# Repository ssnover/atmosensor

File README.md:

# atmosensor
This is a simple project for measuring and recording air quality data from an embedded device.

## Components
* [`atmosensor-fw`](atmosensor-fw/README.md) This contains the embedded firmware application which reads from
the sensors and communicates the data over USB.
* `atmosensor-host-apps` Linux-based applications for interacting with the firmware app.
  * `atmosensor-tui` Text user interface for sending and receiving commands via USB.
* `atmosensor-kicad` KiCAD schematic and PCB layout for the hardware which connects
to the sensors.
* `usb-protocol` Documentation of the protocol being used for communicating between
the host application and the embedded firmware.

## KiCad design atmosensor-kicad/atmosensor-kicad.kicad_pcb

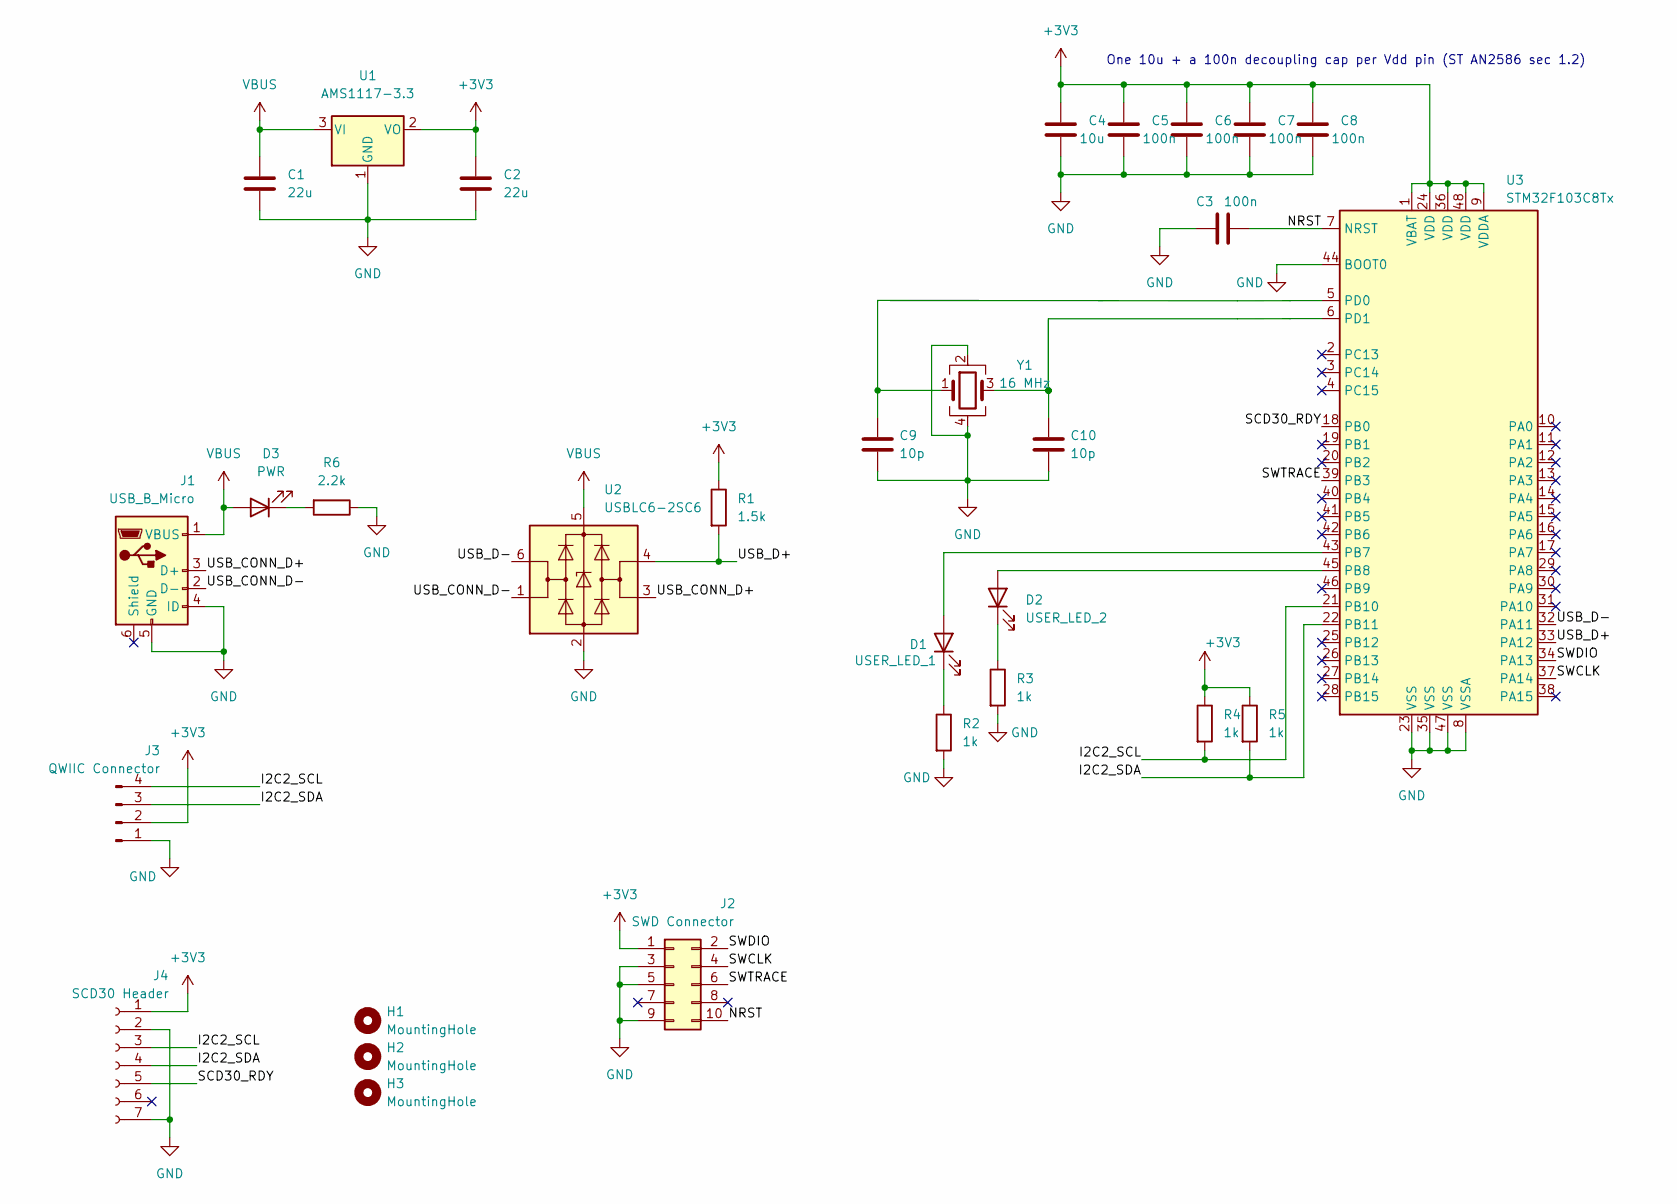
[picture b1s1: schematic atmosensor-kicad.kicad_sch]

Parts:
C1, C2: 22u; C_0603_1608Metric
C3, C5, C6, C7, C8: 100n; C_0402_1005Metric
C4: 10u; C_0603_1608Metric
C9, C10: 10p; C_0402_1005Metric
D1: USER_LED_1; LED_0402_1005Metric
D2: USER_LED_2; LED_0402_1005Metric
D3: PWR; LED_0402_1005Metric
H1, H2, H3: MountingHole; MountingHole_2.2mm_M2
J1: USB_B_Micro; USB_Micro-B_Amphenol_10103594-0001LF_Horizontal
J2: SWD Connector; PinHeader_2x05_P1.27mm_Vertical_SMD
J3: QWIIC Connector; JST_SM04B-SRSS-TB(LF)(SN)
J4: SCD30 Header; PinSocket_1x07_P2.54mm_Vertical
R1: 1.5k; R_0402_1005Metric
R2, R3, R4, R5: 1k; R_0402_1005Metric
R6: 2.2k; R_0402_1005Metric
U1: AMS1117-3.3; SOT-223-3_TabPin2
U2: USBLC6-2SC6; SOT-23-6
U3: STM32F103C8Tx; LQFP-48_7x7mm_P0.5mm
Y1: 16 MHz; Crystal_SMD_3225-4Pin_3.2x2.5mm

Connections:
+3V3: C2.1, C4.1, C5.1, C6.1, C7.1, C8.1, J2.1, J3.2, J4.1, R1.1, R4.1, R5.1, U1.2 (VO), U3.1 (VBAT), U3.9 (VDDA), U3.24 (VDD), U3.36 (VDD), U3.48 (VDD)
/I2C2_SCL: J3.4, J4.3, R4.2, U3.21 (PB10)
/I2C2_SDA: J3.3, J4.4, R5.2, U3.22 (PB11)
/NRST: C3.2, J2.10, U3.7 (NRST)
/SCD30_RDY: J4.5, U3.18 (PB0)
/SWCLK: J2.4, U3.37 (PA14)
/SWDIO: J2.2, U3.34 (PA13)
/SWTRACE: J2.6, U3.39 (PB3)
/USB_CONN_D+: J1.3 (D+), U2.3 (I/O2)
/USB_CONN_D-: J1.2 (D-), U2.1 (I/O1)
/USB_D+: R1.2, U2.4 (I/O2), U3.33 (PA12)
/USB_D-: U2.6 (I/O1), U3.32 (PA11)
GND: C1.2, C2.2, C3.1, C4.2, C5.2, C6.2, C7.2, C8.2, C9.2, C10.2, J1.4 (ID), J1.5 (GND), J2.3, J2.5, J2.9, J3.1, J4.2, J4.7, R2.2, R3.2, R6.1, U1.1 (GND), U2.2 (GND), U3.8 (VSSA), U3.23 (VSS), U3.35 (VSS), U3.44 (BOOT0), U3.47 (VSS), Y1.2, Y1.4
unnamed: C9.1, U3.5 (PD0), Y1.1
unnamed: C10.1, U3.6 (PD1), Y1.3
unnamed: D1.1 (K), R2.1
unnamed: D1.2 (A), U3.43 (PB7)
unnamed: D2.1 (K), R3.1
unnamed: D2.2 (A), U3.45 (PB8)
unnamed: D3.1 (K), R6.2
VBUS: C1.1, D3.2 (A), J1.1 (VBUS), U1.3 (VI), U2.5 (VBUS)

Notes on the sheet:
One 10u + a 100n decoupling cap per Vdd pin (ST AN2586 sec 1.2)

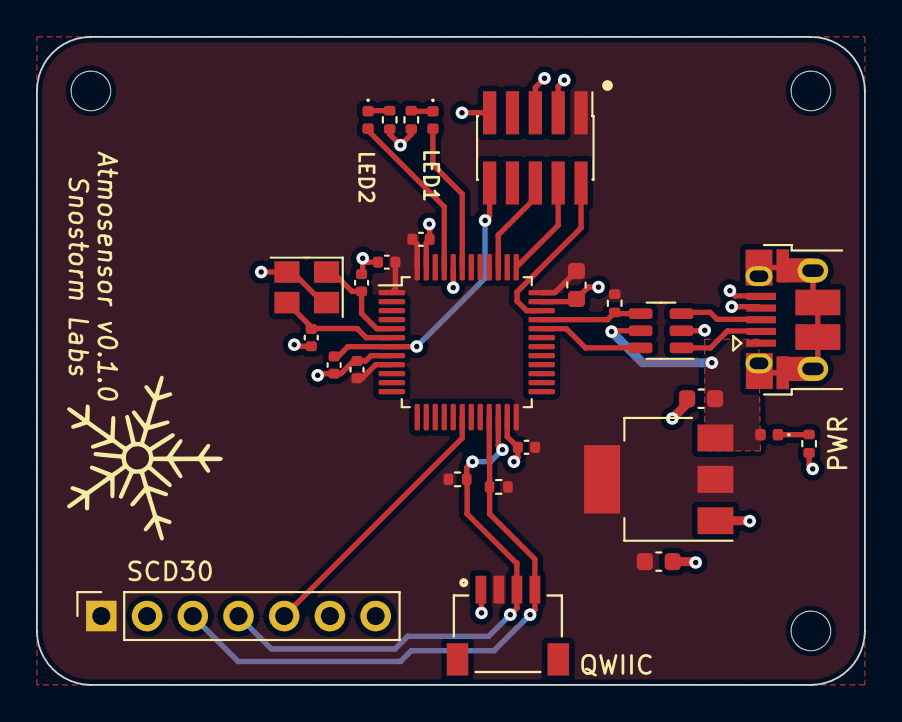
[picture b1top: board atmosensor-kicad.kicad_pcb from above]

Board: 2 copper layers, 46.0 x 36.0 mm, 30 parts (0 on the bottom side), 21 nets.

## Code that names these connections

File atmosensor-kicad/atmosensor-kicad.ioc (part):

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Mcu.Name=STM32F103C(8-B)Tx
Mcu.Package=LQFP48
Mcu.UserName=STM32F103C8Tx
PA11.Mode=Device
PA11.Signal=USB_DM
PA12.Mode=Device
PA12.Signal=USB_DP
PA13.Mode=Trace_Asynchronous_SW
PA13.Signal=SYS_JTMS-SWDIO
PA14.Mode=Trace_Asynchronous_SW
PA14.Signal=SYS_JTCK-SWCLK
PB0.Signal=GPXTI0
PB10.Mode=I2C
PB10.Signal=I2C2_SCL
PB11.Mode=I2C
PB11.Signal=I2C2_SDA
PB3.Mode=Trace_Asynchronous_SW
PB3.Signal=SYS_JTDO-TRACESWO
PB6.GPIOParameters=GPIO_Label
PB6.GPIO_Label=USER_LED_2
PB6.Signal=GPIO_Output
PB7.GPIOParameters=GPIO_Label
PB7.GPIO_Label=USER_LED_1
PB7.Signal=GPIO_Output
PD0-OSC_IN.Mode=HSE-External-Oscillator
PD0-OSC_IN.Signal=RCC_OSC_IN
PD1-OSC_OUT.Mode=HSE-External-Oscillator
PD1-OSC_OUT.Signal=RCC_OSC_OUT
RCC.HSE_VALUE=16000000
RCC.SYSCLKFreq_VALUE=48000000
RCC.SYSCLKSource=RCC_SYSCLKSOURCE_PLLCLK
board=custom

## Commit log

2022-11-05 Initialize the rest of the peripherals
2022-11-11 MONOREPOgit add README.md !
2022-11-20 Finished the TUI part, now just need to add USB tokio context
2022-11-26 Working for basic comms! No COBS for serial protocol yet
2022-11-27 COBS encoding is working and successfully got a pong back from the micro over USB
2022-12-03 Moved all of the encoding and decoding out of the interrupt, but now things are not working...
2022-12-04 USB comms are working again! Without encoding/decoding in an ISR context!
2023-01-07 Get a command queue building and an led module
2023-01-07 Cleanup
2023-01-22 Managed to send a command to sensor based on usb message, but it failed so its logic analyzer time
2023-01-22 Cargo fmt
2023-01-23 Fix dependencies to point at git repos instead of local paths
2023-01-25 Came up with way to not be leaking the actual type of my embedded hal objects
2023-01-29 We now have data which can be queried via usb!
2023-01-29 Fix safety issue with access to command queue in the scd30 data ready interrupt
2023-01-29 Add docs
2023-02-14 Upgrade cortex-m-rt
2023-04-26 Monster commit
2023-05-03 Finish protocol module generator script for host apps
2023-05-03 Finish the protocol generation
2023-05-06 Break into two crates; tools and client
2023-05-06 Use the atmosensor client lib in tui
2023-05-07 Split the atmosensor client into a crate separate from the daemon and encapsulate tokio_serial
2023-05-07 Add influx client to atmosensord, data should be running now
2023-05-08 Set up deployment tools for atmosensord
2023-05-09 Add logging to env_logger and a more sensible app structure
2023-05-09 Add logging to the client reader
2023-05-09 Add timing out
2023-05-09 Add ctrl-c handler
2023-05-09 Try requesting last item perhaps
2023-05-16 Add a yaml config file
2023-05-16 Add some logging to show config on startup
2023-05-16 Fix host in config
2023-05-20 Add commands to the firmware for querying humidity and temperature
2023-05-20 Start requesting and reporting humidity and temperature data
2023-06-18 Add initial attempt at a wifi-mqtt solution for the co2 sensing
